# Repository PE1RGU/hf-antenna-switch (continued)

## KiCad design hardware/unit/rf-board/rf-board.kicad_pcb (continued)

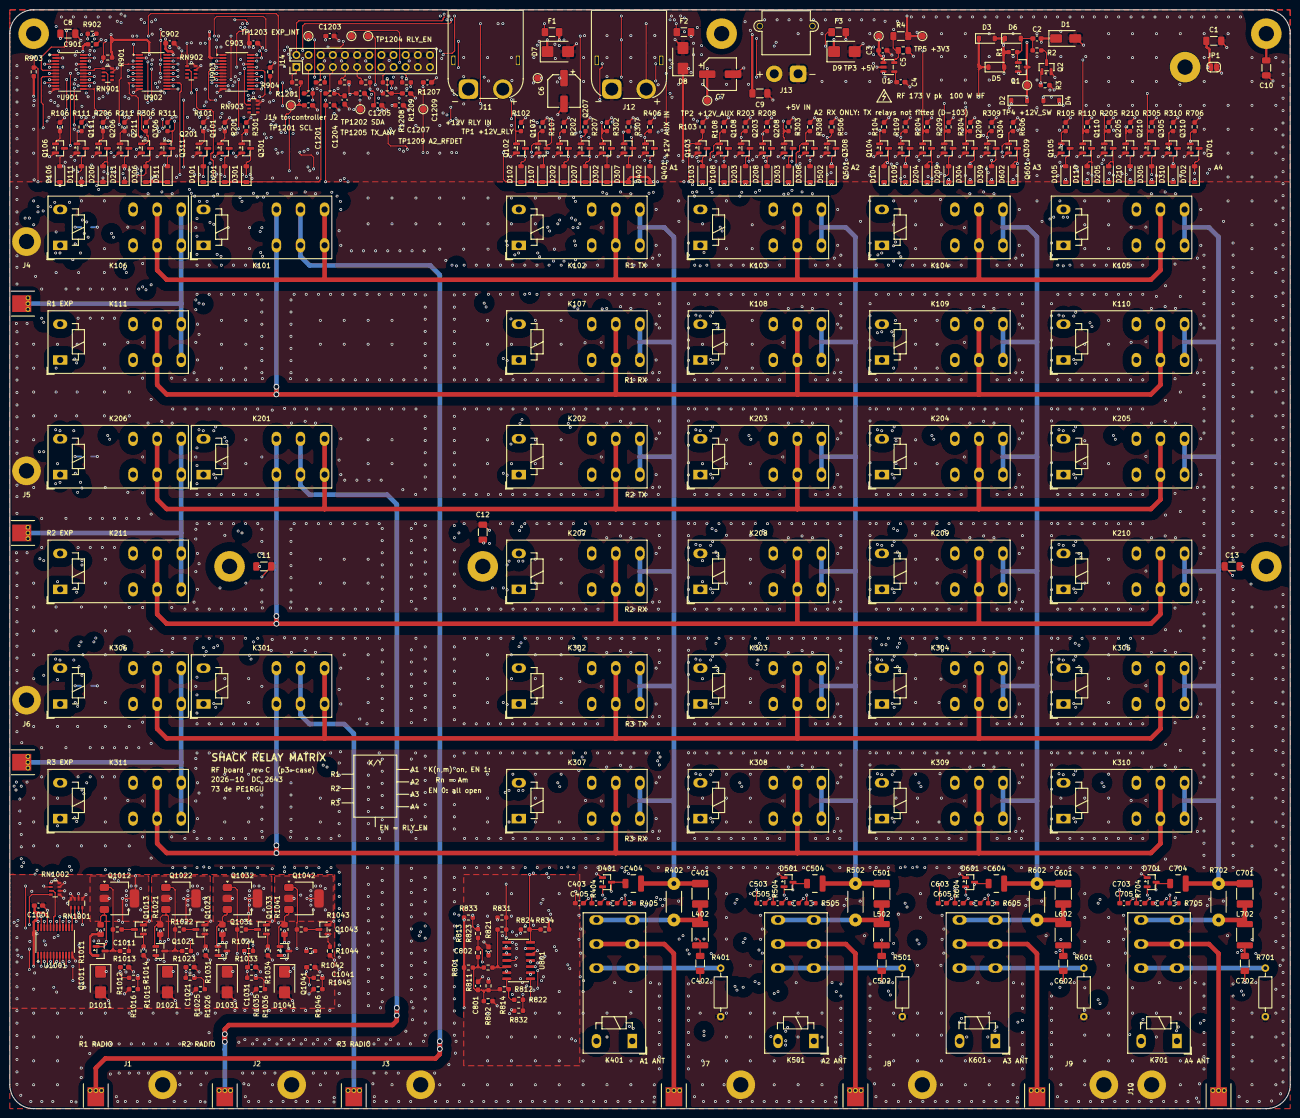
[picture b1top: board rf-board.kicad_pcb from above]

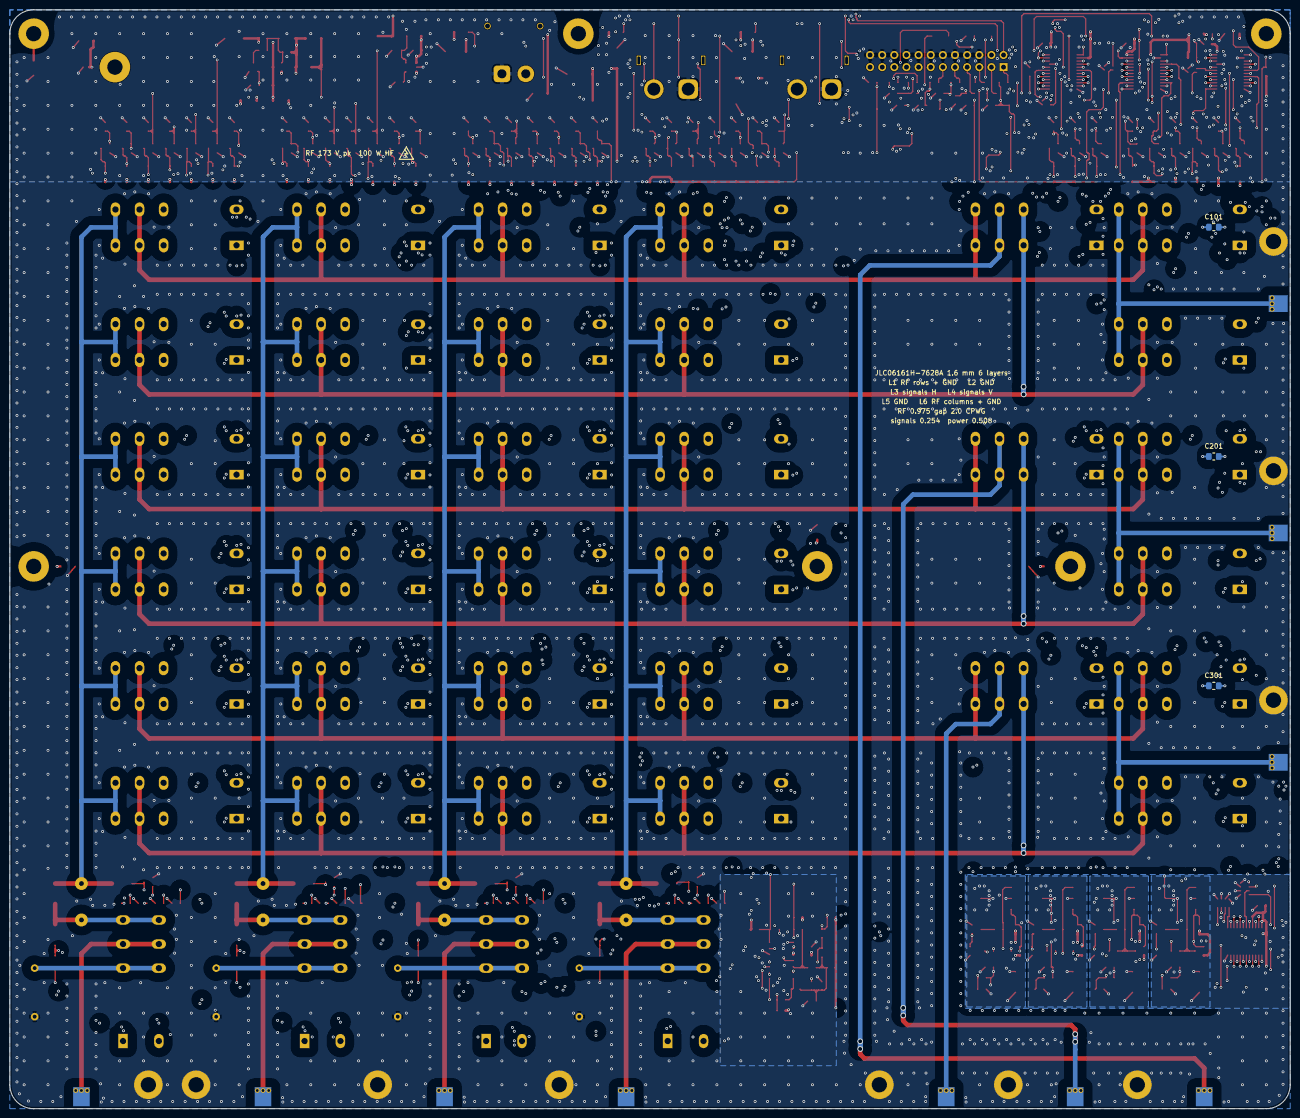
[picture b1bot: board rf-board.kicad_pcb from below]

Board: 6 copper layers, 268.0 x 230.0 mm, 357 parts (3 on the bottom side), 197 nets.

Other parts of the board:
CTL3D: controller board 3D (reference only)

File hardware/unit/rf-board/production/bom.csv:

Designator,Footprint,Quantity,Value,LCSC Part #
"C1001, C3, C802, C901, C902, C903",0603,6,1u 16V X7R,
"C101, C201, C301",0805,3,1u 50V X7R,
"C1011, C1021, C1031, C1041, C801",0603,5,100n 50V X7R,
"C4, C403, C503, C603, C703",0603,5,10n 50V X7R,
"C404, C504, C604, C704",1206,4,4.7p 1kV C0G,
"C405, C505, C605, C705",0603,4,47p 50V C0G,
C5,0805,1,4.7u 16V X7R,
"C6, C7",CP_Elec_6.3x7.7,2,47u 25V polymer,
D1,D_SMA,1,SS14,
"D101, D102, D104, D105, D106, D107, D108, D109, D110, D111, D201, D202, D204, D205, D206, D207, D208, D209, D210, D211, D301, D302, D304, D305, D306, D307, D308, D309, D310, D311, D402, D502, D602, D702",D_SOD-123,34,1N4148W,
"D1011, D1021, D1031, D1041, D7, D8",D_SMB,6,SMBJ15A,
"D2, D3, D4, D5",D_SOD-123,4,BZT52C24,
"D401, D501, D601, D701",SOT-23,4,BAS70-04,
D6,D_SOD-123,1,BZT52C15,
D9,D_SMB,1,SMBJ6.0A,
"F1, F2, F3",1206,3,1A T,
"J1, J2, J3, J7, J8, J9",SO239_83-798_StrapPad_BossRight,6,83-798 SO-239,
J10,SO239_83-798_StrapPad_BossLeft,1,83-798 SO-239,
"J11, J12",AMASS_XT60PW-M_1x02_P7.20mm_Horizontal,2,XT60PW-M,
J13,AMASS_XT30PW-M_1x02_P2.50mm_Horizontal,1,XT30PW-M,
J14,PinHeader_2x12_P2.54mm_Vertical,1,Controller header,
"J4, J5, J6",SMA_901-9215_StrapPad,3,SMA jack EXP,
"K101, K102, K104, K105, K106, K107, K108, K109, K110, K111, K201, K202, K204, K205, K206, K207, K208, K209, K210, K211, K301, K302, K304, K305, K306, K307, K308, K309, K310, K311, K401, K501, K601, K701",Relay_SPDT_Schrack-RT1-16A-FormC_RM5mm,34,RTD14012F,
Q1,SOT-23,1,PMV50EPEA,
"Q101, Q1013, Q102, Q1023, Q1033, Q104, Q1043, Q105, Q106, Q107, Q108, Q109, Q110, Q111, Q2, Q201, Q202, Q204, Q205, Q206, Q207, Q208, Q209, Q210, Q211, Q301, Q302, Q304, Q305, Q306, Q307, Q308, Q309, Q310, Q311, Q401, Q501, Q601, Q701",SOT-23,39,BSS138BK,
"Q1011, Q1021, Q1031, Q1041",SOT-23,4,BC857B,
"Q1012, Q1022, Q1032, Q1042",SOT-223-3_TabPin2,4,IRFL9014,
"R1, R1016, R1026, R1036, R1046, R801, R811, R812, R813, R814, R831, R832, R833, R834, R903",0603,15,10k,
"R101, R1012, R1014, R102, R1022, R1024, R1032, R1034, R104, R1042, R1044, R105, R106, R107, R108, R109, R110, R111, R201, R202, R204, R205, R206, R207, R208, R209, R210, R211, R3, R301, R302, R304, R305, R306, R307, R308, R309, R310, R311, R406, R506, R606, R706, R904",0603,44,100k,
"R1011, R1021, R1031, R1041",0805,4,10R,
"R1013, R1023, R1033, R1043, R404, R405, R504, R505, R604, R605, R704, R705",0603,12,47k,
"R1015, R1025, R1035, R1045",0603,4,33k,
"R1201, R1202, R1203, R1204, R1205, R1206, R1207, R1208, R1209",0603,9,0R,
"R2, R901, R902",0603,3,2k2,
R4,1206,1,0R,
"R401, R501, R601, R701",R_Axial_DIN0207_L6.3mm_D2.5mm_P10.16mm_Horizontal,4,1M HV,
"R402, R502, R602, R702",WireLink_P7.62mm_D1.0mm,4,0R wire link,
R802,0603,1,1k,
"R821, R822, R823, R824",0603,4,1M,
"RN1001, RN1002, RN901, RN902, RN903",R_Array_Convex_4x0603,5,10k x4,
U1,SOT-23-5,1,LP2985-33,
"U1001, U901, U902, U903",TSSOP-24_4.4x7.8mm_P0.65mm,4,PCA9539,
U801,SOIC-14_3.9x8.7mm_P1.27mm,1,LM2901,

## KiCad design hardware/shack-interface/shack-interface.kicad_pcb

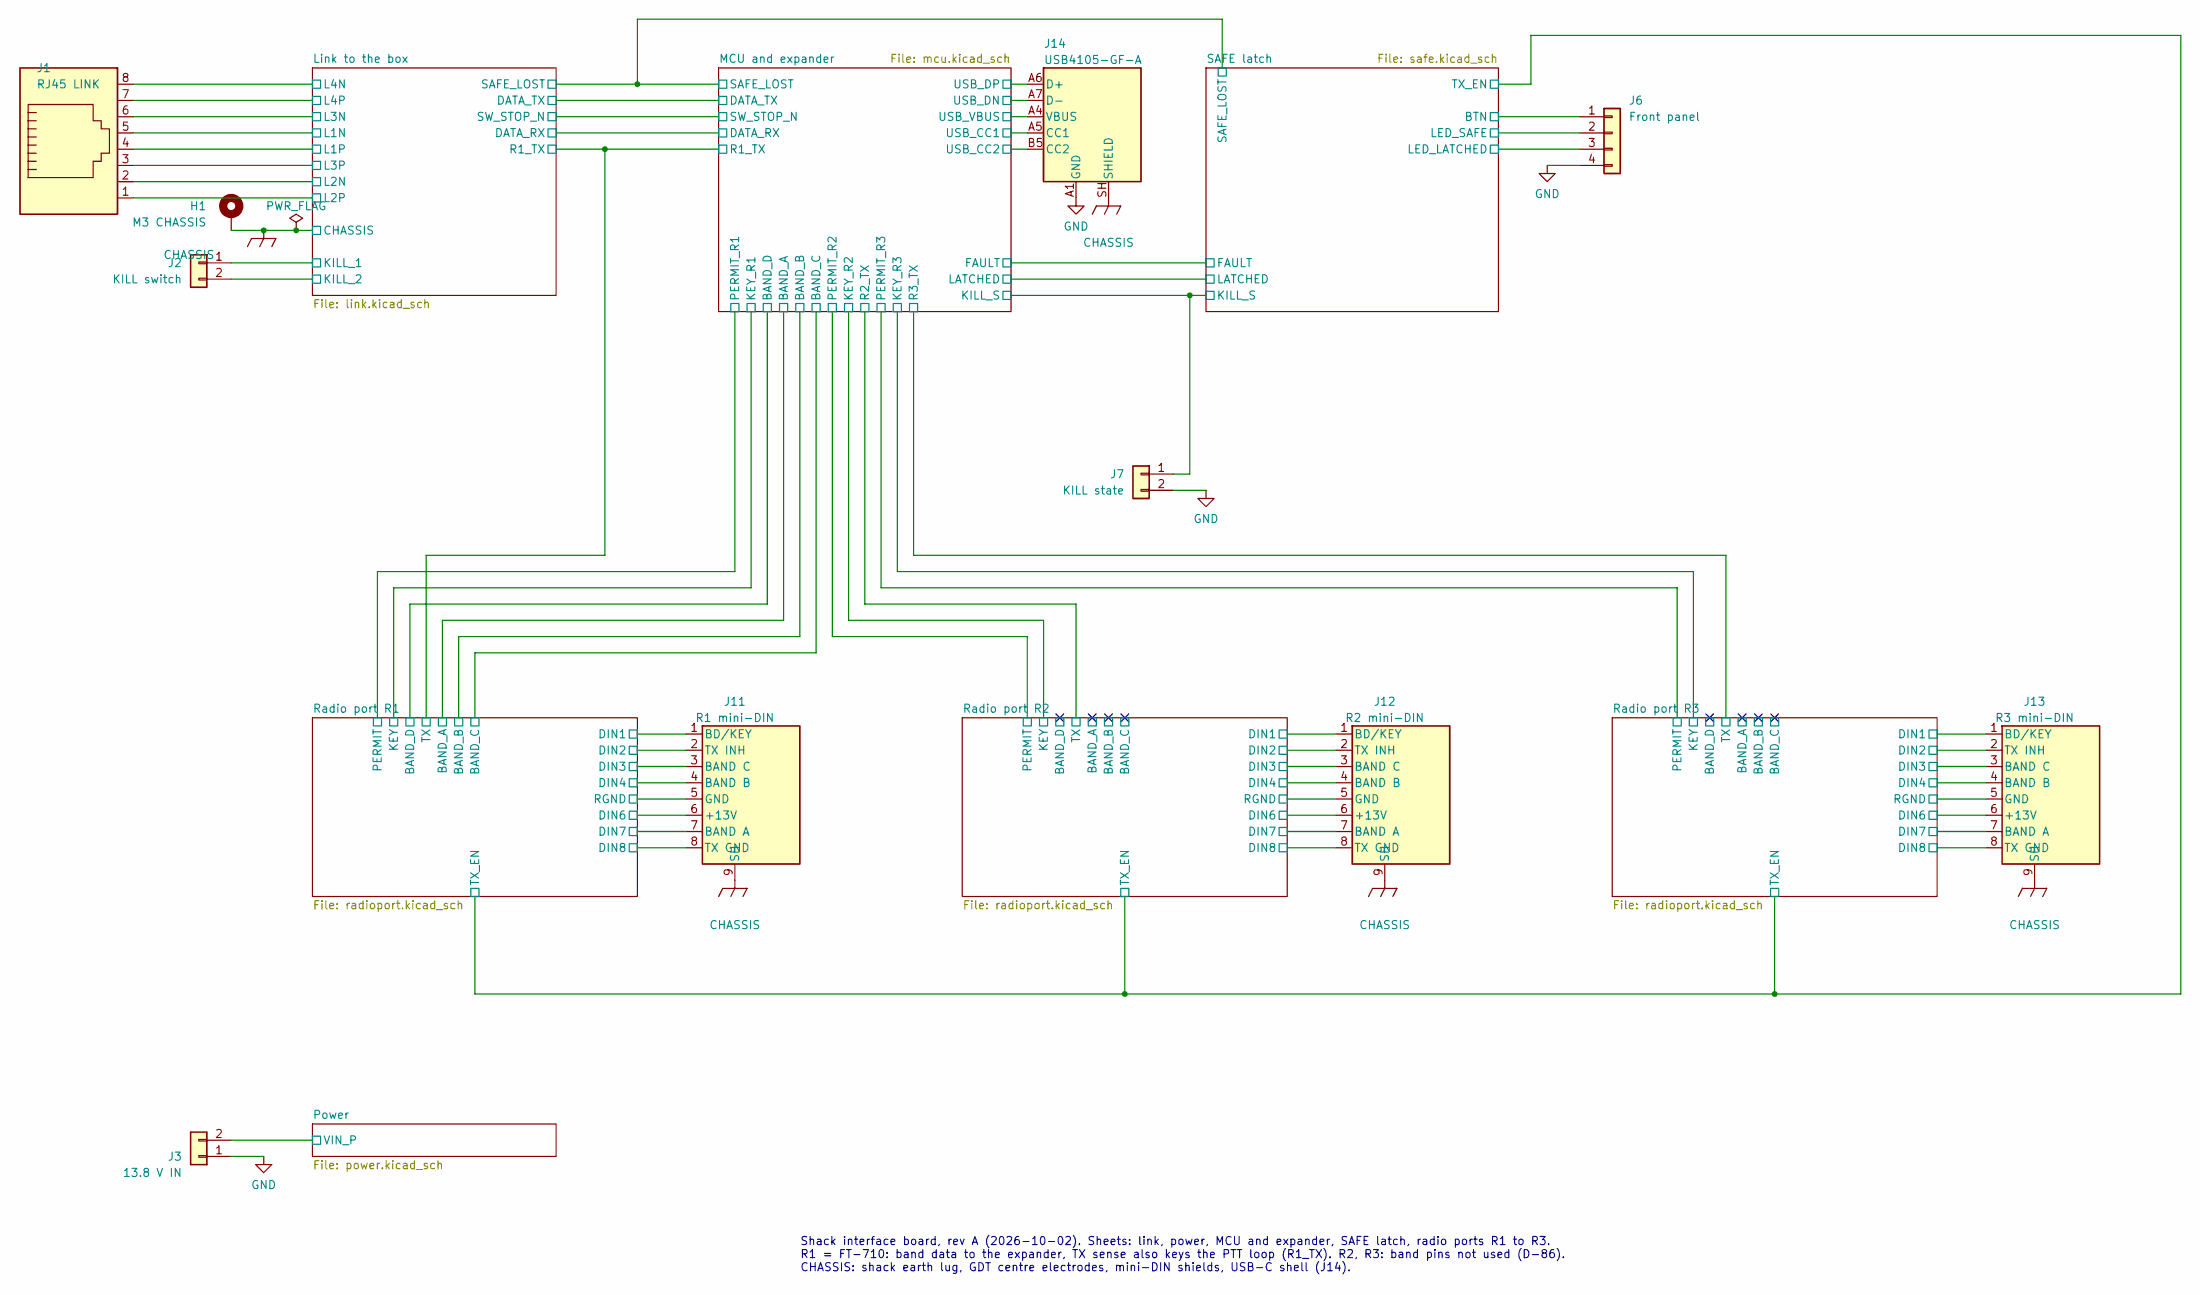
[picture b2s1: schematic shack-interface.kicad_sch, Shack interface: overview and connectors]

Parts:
H1: M3 CHASSIS; MountingHole_3.2mm_M3_Pad
J1: RJ45 LINK; RJ45_8P8C_Unshielded_TabDown; MPN 615008137121
J2: KILL switch; JST_XH_B2B-XH-A_1x02_P2.50mm_Vertical
J3: 13.8 V IN; AMASS_XT60PW-M_1x02_P7.20mm_Horizontal; MPN XT60PW-M
J6: Front panel; JST_XH_B4B-XH-A_1x04_P2.50mm_Vertical
J7: KILL state; JST_XH_B2B-XH-A_1x02_P2.50mm_Vertical
J11: R1 mini-DIN; MiniDIN-8_SameSky_MD-80SM_Horizontal; MPN MD-80SM
J12: R2 mini-DIN; MiniDIN-8_SameSky_MD-80SM_Horizontal; MPN MD-80SM
J13: R3 mini-DIN; MiniDIN-8_SameSky_MD-80SM_Horizontal; MPN MD-80SM
J14: USB4105-GF-A; USB_C_Receptacle_GCT_USB4105-xx-A_16P_TopMnt_Horizontal; MPN USB4105-GF-A

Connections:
/Link to the box/KILL_1: J2.1; also elsewhere on the board
/Link to the box/KILL_2: J2.2; also elsewhere on the board
/Link to the box/L1N: J1.5; also elsewhere on the board
/Link to the box/L1P: J1.4; also elsewhere on the board
/Link to the box/L2N: J1.2; also elsewhere on the board
/Link to the box/L2P: J1.1; also elsewhere on the board
/Link to the box/L3N: J1.6; also elsewhere on the board
/Link to the box/L3P: J1.3; also elsewhere on the board
/Link to the box/L4N: J1.8; also elsewhere on the board
/Link to the box/L4P: J1.7; also elsewhere on the board
/MCU and expander/KILL_S: J7.1; also elsewhere on the board
/MCU and expander/USB_CC1: J14.A5 (CC1); also elsewhere on the board
/MCU and expander/USB_CC2: J14.B5 (CC2); also elsewhere on the board
/MCU and expander/USB_DN: J14.A7 (D-), J14.B7 (D-); also elsewhere on the board
/MCU and expander/USB_DP: J14.A6 (D+), J14.B6 (D+); also elsewhere on the board
/MCU and expander/USB_VBUS: J14.A4 (VBUS), J14.A9 (VBUS), J14.B4 (VBUS), J14.B9 (VBUS); also elsewhere on the board
/Power/VIN_P: J3.2; also elsewhere on the board
/Radio port R1/DIN1: J11.1 (BD/KEY); also elsewhere on the board
/Radio port R1/DIN2: J11.2 (TX INH); also elsewhere on the board
/Radio port R1/DIN3: J11.3 (BAND C); also elsewhere on the board
/Radio port R1/DIN4: J11.4 (BAND B); also elsewhere on the board
/Radio port R1/DIN6: J11.6 (+13V); also elsewhere on the board
/Radio port R1/DIN7: J11.7 (BAND A); also elsewhere on the board
/Radio port R1/DIN8: J11.8 (TX GND); also elsewhere on the board
/Radio port R1/RGND: J11.5 (GND); also elsewhere on the board
/Radio port R2/DIN1: J12.1 (BD/KEY); also elsewhere on the board
/Radio port R2/DIN2: J12.2 (TX INH); also elsewhere on the board
/Radio port R2/DIN3: J12.3 (BAND C); also elsewhere on the board
/Radio port R2/DIN4: J12.4 (BAND B); also elsewhere on the board
/Radio port R2/DIN6: J12.6 (+13V); also elsewhere on the board
/Radio port R2/DIN7: J12.7 (BAND A); also elsewhere on the board
/Radio port R2/DIN8: J12.8 (TX GND); also elsewhere on the board
/Radio port R2/RGND: J12.5 (GND); also elsewhere on the board
/Radio port R3/DIN1: J13.1 (BD/KEY); also elsewhere on the board
/Radio port R3/DIN2: J13.2 (TX INH); also elsewhere on the board
/Radio port R3/DIN3: J13.3 (BAND C); also elsewhere on the board
/Radio port R3/DIN4: J13.4 (BAND B); also elsewhere on the board
/Radio port R3/DIN6: J13.6 (+13V); also elsewhere on the board
/Radio port R3/DIN7: J13.7 (BAND A); also elsewhere on the board
/Radio port R3/DIN8: J13.8 (TX GND); also elsewhere on the board
/Radio port R3/RGND: J13.5 (GND); also elsewhere on the board
/SAFE latch/BTN: J6.1; also elsewhere on the board
/SAFE latch/LED_LATCHED: J6.3; also elsewhere on the board
/SAFE latch/LED_SAFE: J6.2; also elsewhere on the board
CHASSIS: H1.1, J11.9 (SH), J12.9 (SH), J13.9 (SH), J14.SH (SHIELD); also elsewhere on the board
GND: J3.1, J6.4, J7.2, J14.A1 (GND), J14.A12 (GND), J14.B1 (GND), J14.B12 (GND); also elsewhere on the board

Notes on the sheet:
Shack interface board, rev A (2026-10-02). Sheets: link, power, MCU and expander, SAFE latch, radio ports R1 to R3. R1 = FT-710: band data to the expander, TX sense also keys the PTT loop (R1_TX). R2, R3: band pins not used (D-86). CHASSIS: shack earth lug, GDT centre electrodes, mini-DIN shields, 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

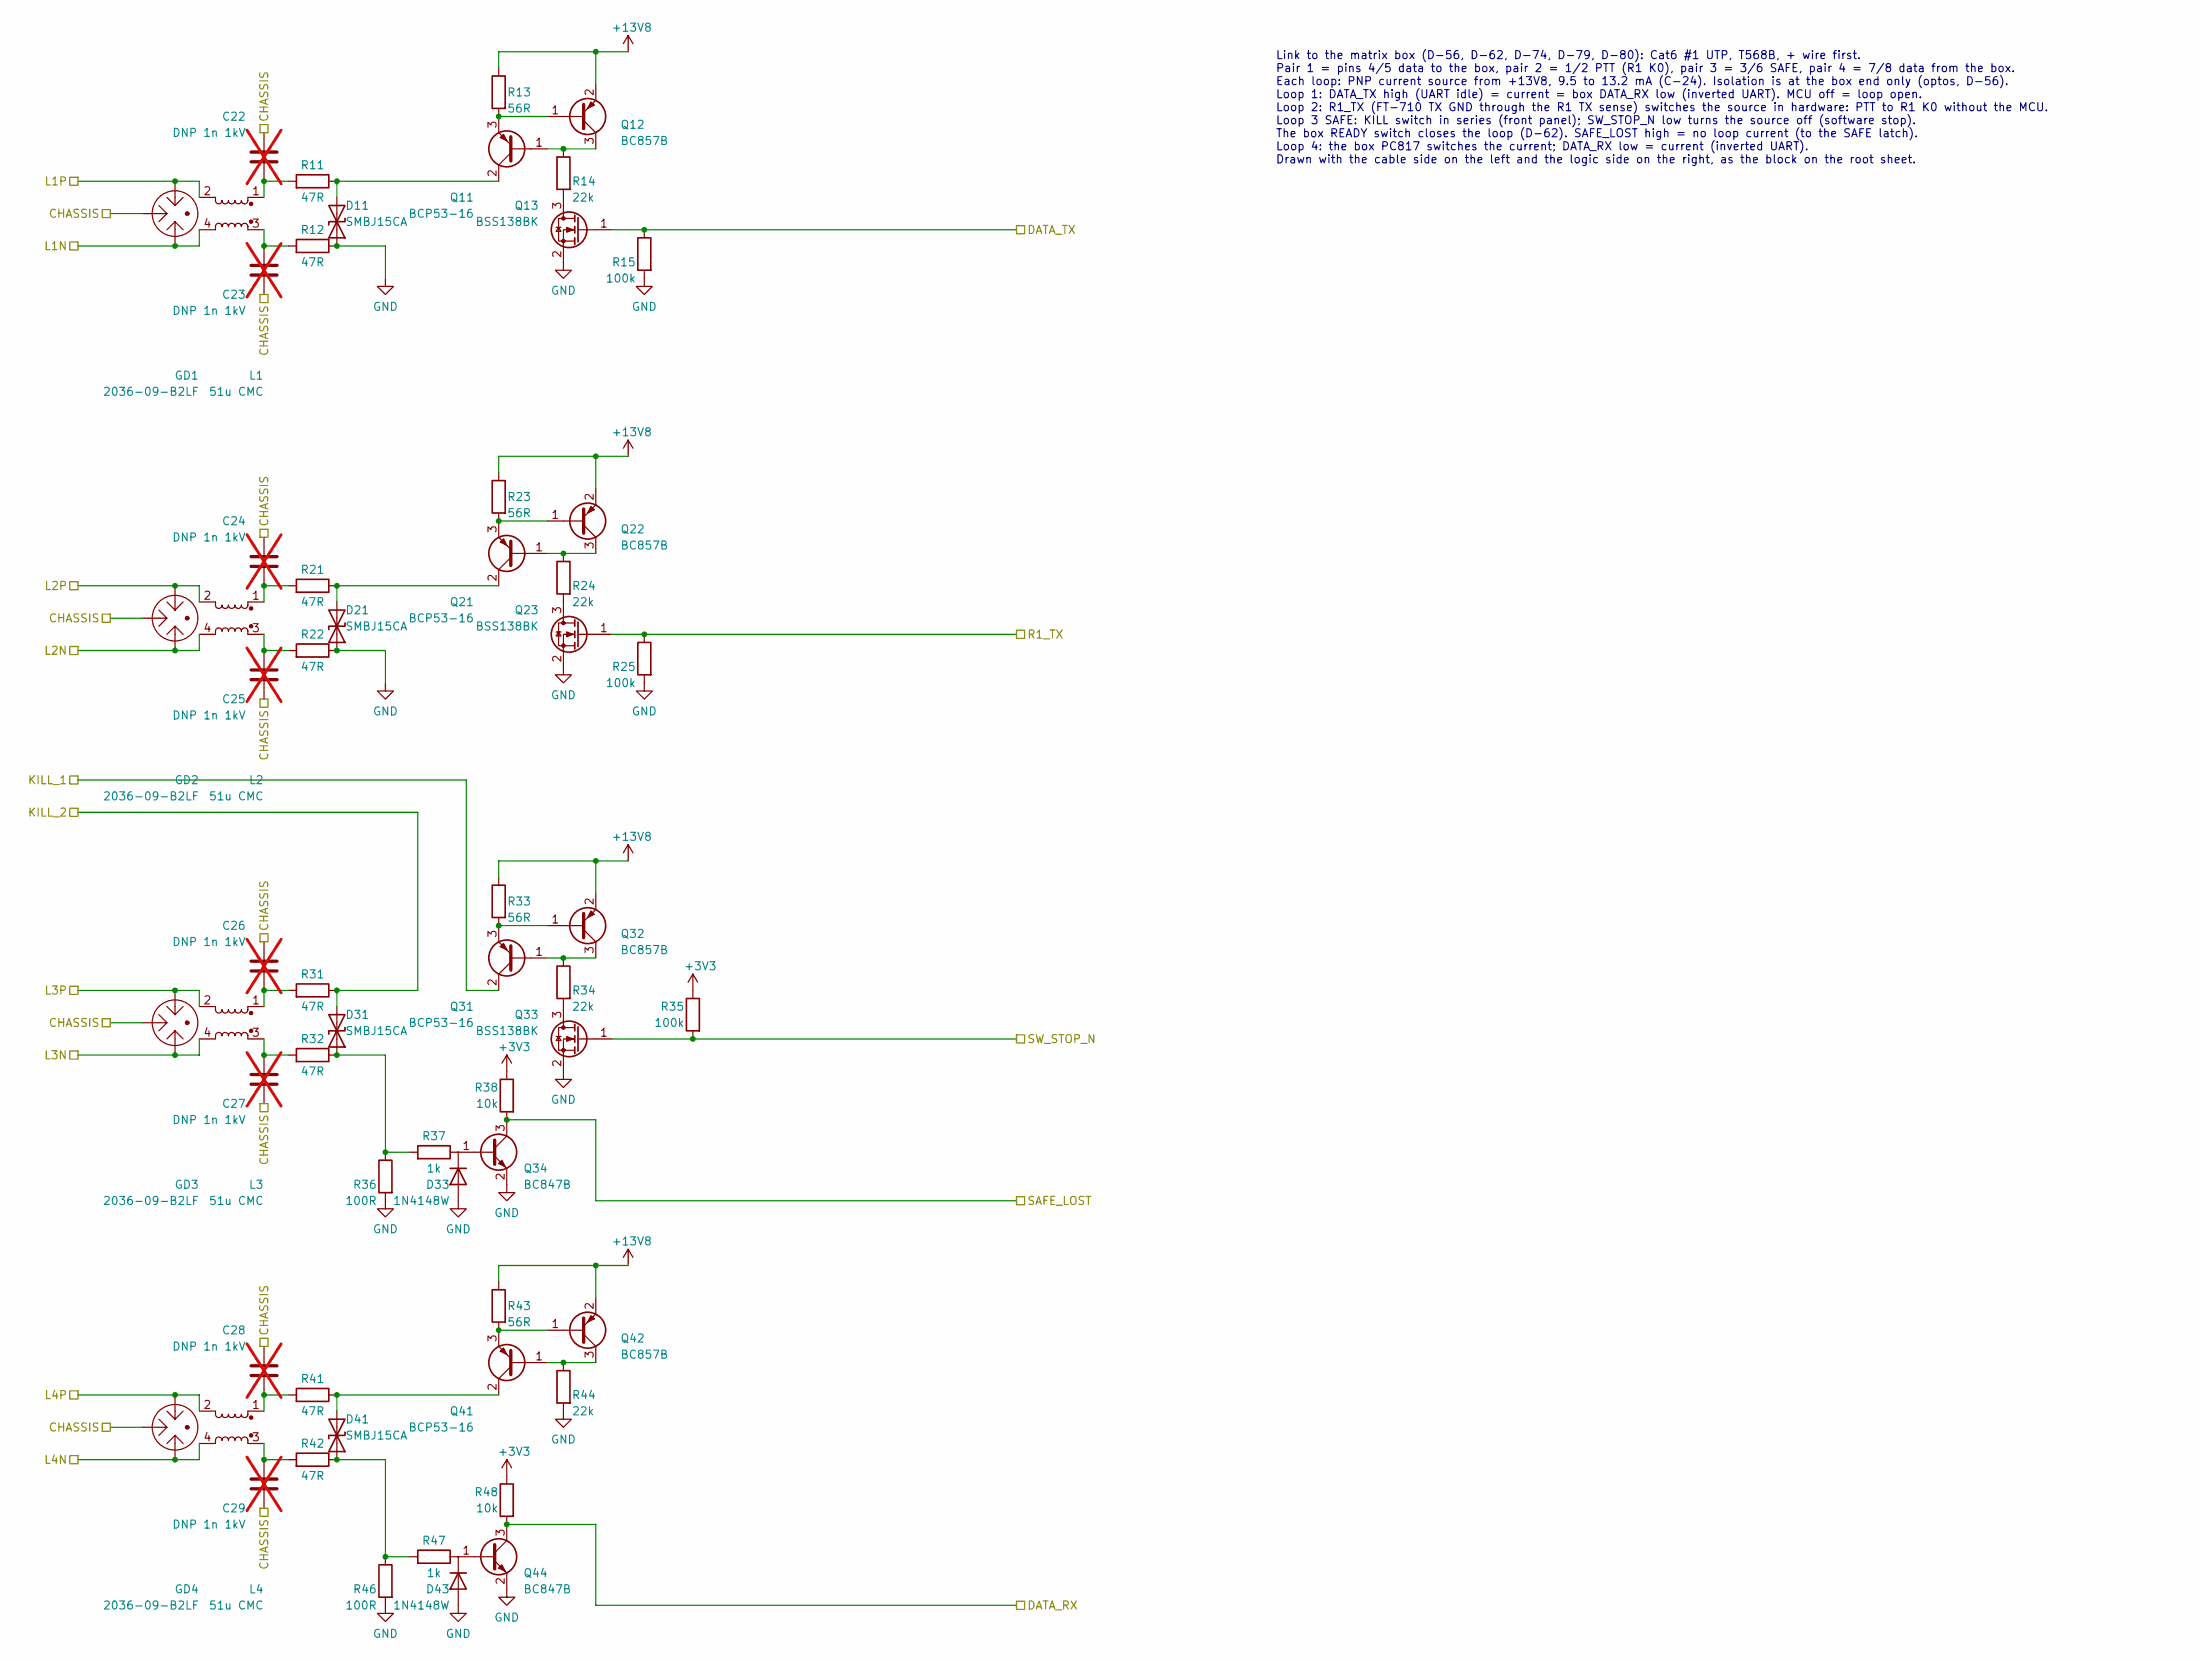
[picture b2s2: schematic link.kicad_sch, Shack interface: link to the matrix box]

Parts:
C22, C23, C24, C25, C26, C27, C28, C29: DNP 1n 1kV; C_1206_3216Metric_Pad1.33x1.80mm_HandSolder; not fitted
D11, D21, D31, D41: SMBJ15CA; D_SMB; MPN SMBJ15CA
D33, D43: 1N4148W; D_SOD-123; MPN 1N4148W
GD1, GD2, GD3, GD4: 2036-09-B2LF; GDT_3Pin_P4.40mm_Bourns-2036-B2_Littelfuse-SL1003A-R; MPN 2036-09-B2LF
L1, L2, L3, L4: 51u CMC; L_CMC_TDK_ACT45B; MPN ACT45B-510-2P-TL003
Q11, Q21, Q31, Q41: BCP53-16; SOT-223-3_TabPin2; MPN BCP53-16
Q12, Q22, Q32, Q42: BC857B; SOT-23; MPN BC857B
Q13, Q23, Q33: BSS138BK; SOT-23; MPN BSS138BK
Q34, Q44: BC847B; SOT-23; MPN BC847B
R11, R12, R21, R22, R31, R32, R41, R42: 47R; R_MELF_MMB-0207
R13, R23, R33, R43: 56R; R_0603_1608Metric_Pad0.98x0.95mm_HandSolder
R14, R24, R34, R44: 22k; R_0603_1608Metric_Pad0.98x0.95mm_HandSolder
R15, R25, R35: 100k; R_0603_1608Metric_Pad0.98x0.95mm_HandSolder
R36, R46: 100R; R_0603_1608Metric_Pad0.98x0.95mm_HandSolder
R37, R47: 1k; R_0603_1608Metric_Pad0.98x0.95mm_HandSolder
R38, R48: 10k; R_0603_1608Metric_Pad0.98x0.95mm_HandSolder

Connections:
+3V3: R35.1, R38.1, R48.1; also elsewhere on the board
+13V8: Q12.2 (E), Q22.2 (E), Q32.2 (E), Q42.2 (E), R13.1, R23.1, R33.1, R43.1; also elsewhere on the board
/Link to the box/KILL_1: Q31.2 (C); also elsewhere on the board
/Link to the box/KILL_2: D31.2 (A2), R31.1; also elsewhere on the board
/Link to the box/L1N: GD1.1, L1.4; also elsewhere on the board
/Link to the box/L1P: GD1.3, L1.2; also elsewhere on the board
/Link to the box/L2N: GD2.1, L2.4; also elsewhere on the board
/Link to the box/L2P: GD2.3, L2.2; also elsewhere on the board
/Link to the box/L3N: GD3.1, L3.4; also elsewhere on the board
/Link to the box/L3P: GD3.3, L3.2; also elsewhere on the board
/Link to the box/L4N: GD4.1, L4.4; also elsewhere on the board
/Link to the box/L4P: GD4.3, L4.2; also elsewhere on the board
/Link to the box/R1_TX: Q23.1 (G), R25.1; also elsewhere on the board
/Link to the box/SW_STOP_N: Q33.1 (G), R35.2; also elsewhere on the board
/MCU and expander/DATA_RX: Q44.3 (C), R48.2; also elsewhere on the board
/MCU and expander/DATA_TX: Q13.1 (G), R15.1; also elsewhere on the board
/MCU and expander/SAFE_LOST: Q34.3 (C), R38.2; also elsewhere on the board
CHASSIS: C22.1, C23.2, C24.1, C25.2, C26.1, C27.2, C28.1, C29.2, GD1.2, GD2.2, GD3.2, GD4.2; also elsewhere on the board
GND: D11.1 (A1), D21.1 (A1), D33.2 (A), D43.2 (A), Q13.2 (S), Q23.2 (S), Q33.2 (S), Q34.2 (E), Q44.2 (E), R12.1, R15.2, R22.1, R25.2, R36.2, R44.2, R46.2; also elsewhere on the board
unnamed: C22.2, L1.1, R11.2
unnamed: C23.1, L1.3, R12.2
unnamed: C24.2, L2.1, R21.2
unnamed: C25.1, L2.3, R22.2
unnamed: C26.2, L3.1, R31.2
unnamed: C27.1, L3.3, R32.2
unnamed: C28.2, L4.1, R41.2
unnamed: C29.1, L4.3, R42.2
unnamed: D11.2 (A2), Q11.2 (C), R11.1
unnamed: D21.2 (A2), Q21.2 (C), R21.1
unnamed: D31.1 (A1), R32.1, R36.1, R37.2
unnamed: D33.1 (K), Q34.1 (B), R37.1
unnamed: D41.1 (A1), R42.1, R46.1, R47.2
unnamed: D41.2 (A2), Q41.2 (C), R41.1
unnamed: D43.1 (K), Q44.1 (B), R47.1
unnamed: Q11.1 (B), Q12.3 (C), R14.1
unnamed: Q11.3 (E), Q12.1 (B), R13.2
unnamed: Q13.3 (D), R14.2
unnamed: Q21.1 (B), Q22.3 (C), R24.1
unnamed: Q21.3 (E), Q22.1 (B), R23.2
unnamed: Q23.3 (D), R24.2
unnamed: Q31.1 (B), Q32.3 (C), R34.1
unnamed: Q31.3 (E), Q32.1 (B), R33.2
unnamed: Q33.3 (D), R34.2
unnamed: Q41.1 (B), Q42.3 (C), R44.1
unnamed: Q41.3 (E), Q42.1 (B), R43.2

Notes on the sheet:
Link to the matrix box (D-56, D-62, D-74, D-79, D-80): Cat6 #1 UTP, T568B, + wire first. Pair 1 = pins 4/5 data to the box, pair 2 = 1/2 PTT (R1 K0), pair 3 = 3/6 SAFE, pair 4 = 7/8 data from the box. Each loop: PNP current source from +13V8, 9.5 to 13.2 mA (C-24). Isolation is at the box end only 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

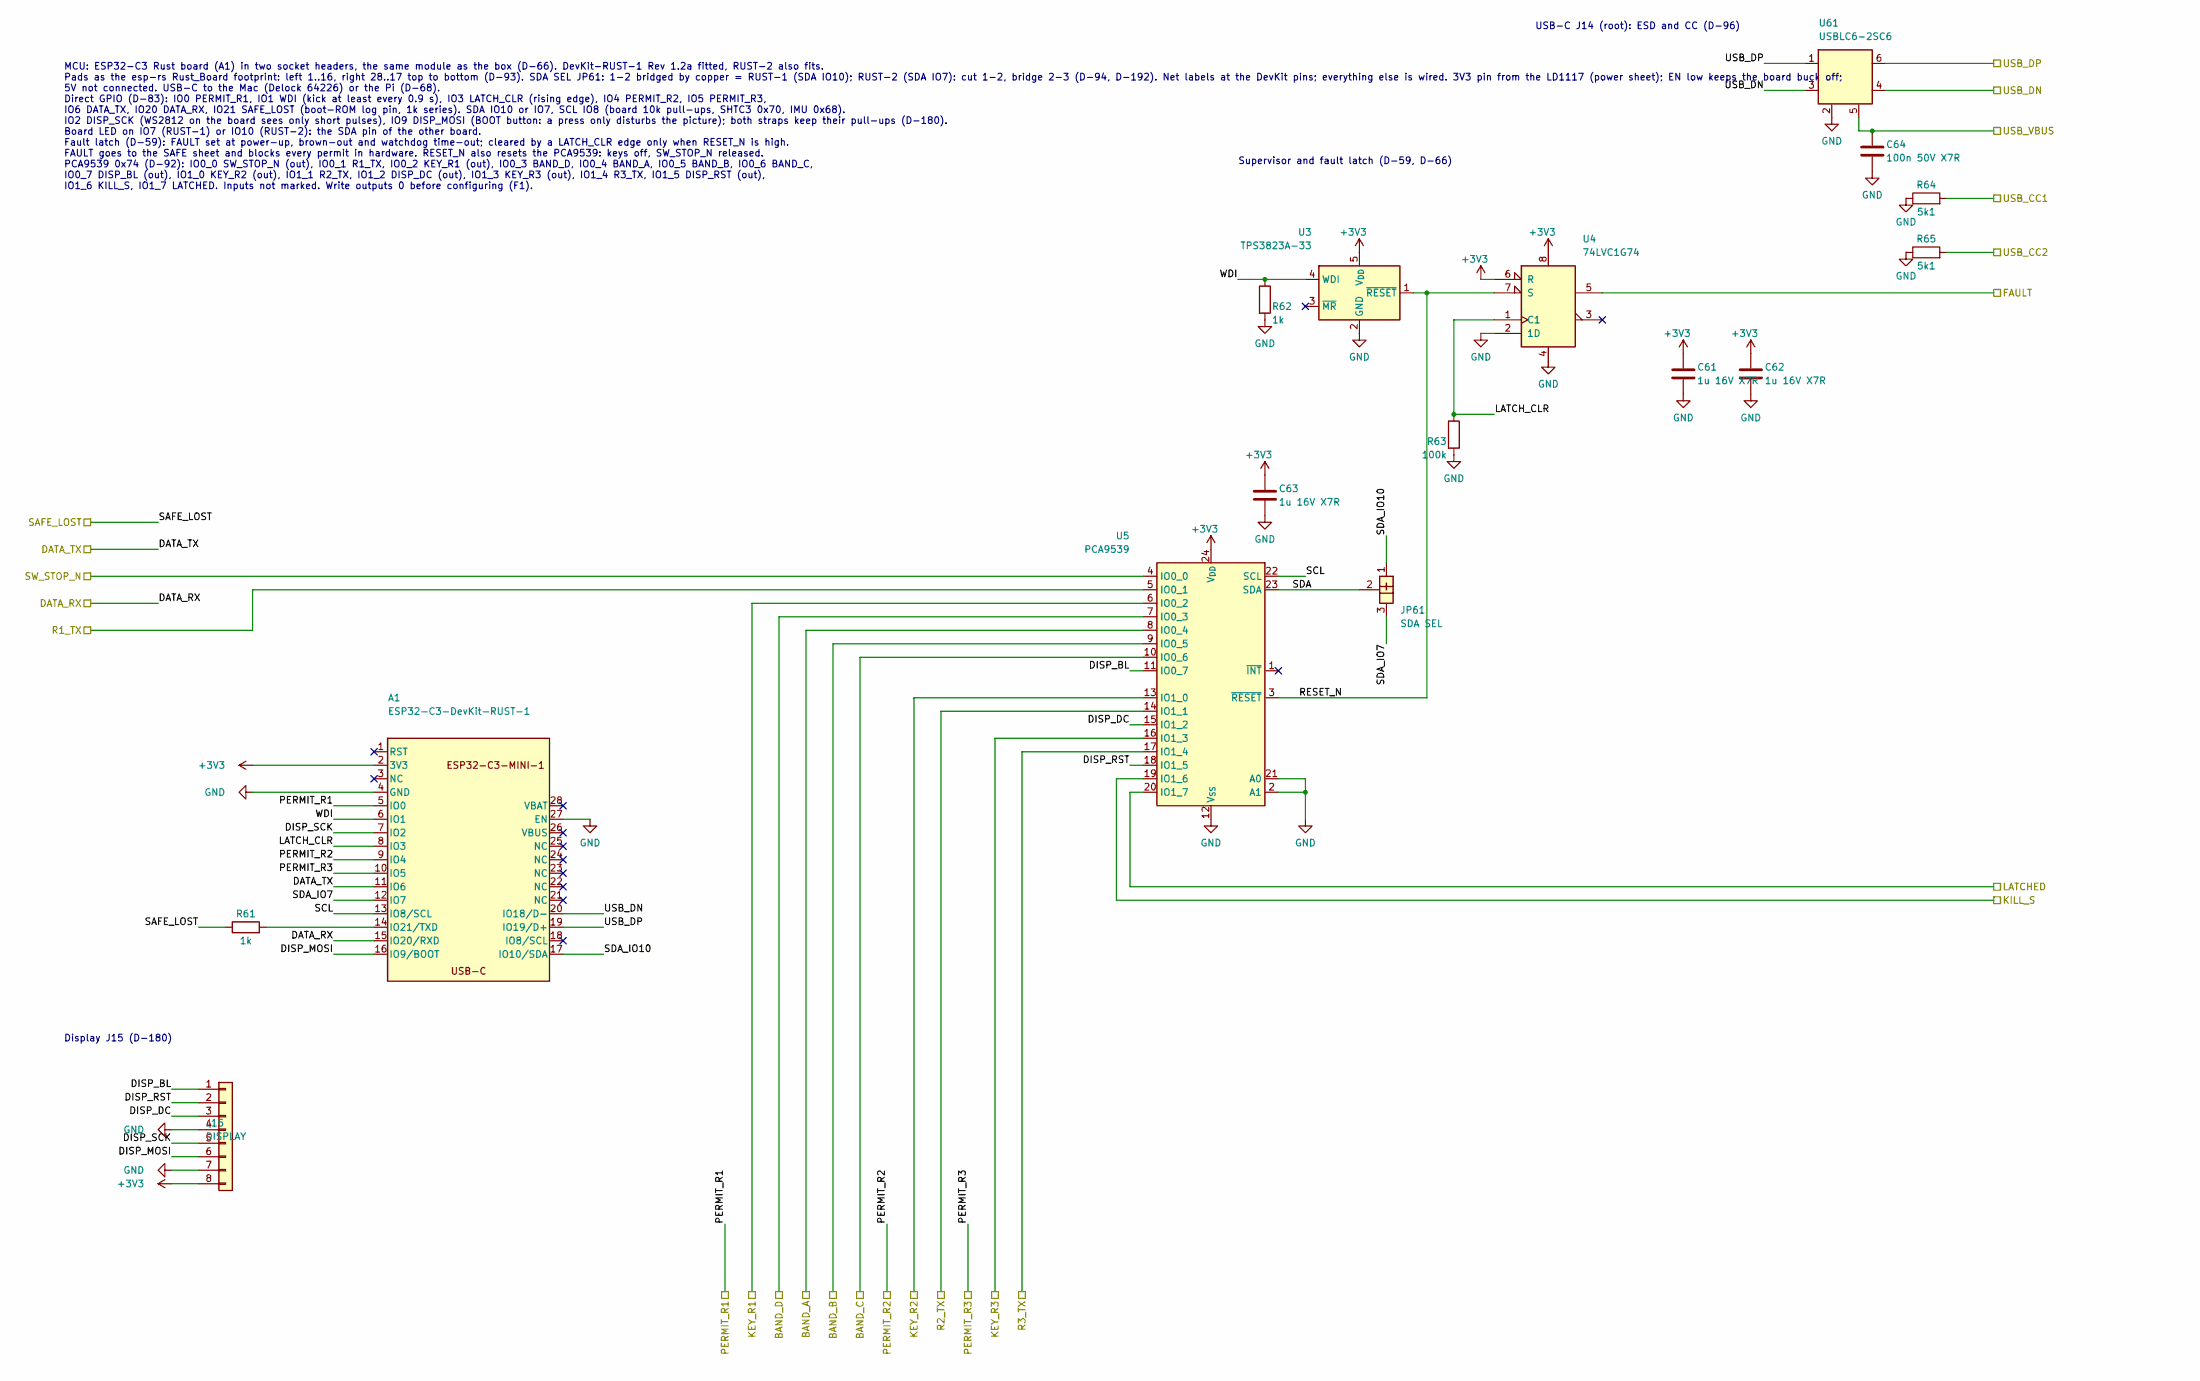
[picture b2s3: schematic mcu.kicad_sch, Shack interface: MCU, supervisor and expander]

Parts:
A1: ESP32-C3-DevKit-RUST-1; ESP32-C3-DevKit-RUST_Socket
C61, C62, C63: 1u 16V X7R; C_0603_1608Metric_Pad1.08x0.95mm_HandSolder
C64: 100n 50V X7R; C_0603_1608Metric_Pad1.08x0.95mm_HandSolder
J15: DISPLAY; PinHeader_1x08_P2.54mm_Vertical
JP61: SDA SEL; SolderJumper-3_P1.3mm_Bridged12_RoundedPad1.0x1.5mm_NumberL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
R61, R62: 1k; R_0603_1608Metric_Pad0.98x0.95mm_HandSolder
R63: 100k; R_0603_1608Metric_Pad0.98x0.95mm_HandSolder
R64, R65: 5k1; R_0603_1608Metric_Pad0.98x0.95mm_HandSolder
U3: TPS3823A-33; SOT-23-5; MPN TPS3823A-33DBVR
U4: 74LVC1G74; VSSOP-8_2.3x2mm_P0.5mm; MPN SN74LVC1G74DCUR
U5: PCA9539; TSSOP-24_4.4x7.8mm_P0.65mm; MPN PCA9539PW,118
U61: USBLC6-2SC6; SOT-23-6; MPN USBLC6-2SC6

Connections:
+3V3: A1.2 (3V3), C61.1, C62.1, C63.1, J15.8, U3.5 (V_{DD}), U4.6 (R), U4.8, U5.24 (V_{DD}); also elsewhere on the board
/Link to the box/R1_TX: U5.5 (IO0_1); also elsewhere on the board
/Link to the box/SW_STOP_N: U5.4 (IO0_0); also elsewhere on the board
/MCU and expander/BAND_A: U5.8 (IO0_4); also elsewhere on the board
/MCU and expander/BAND_B: U5.9 (IO0_5); also elsewhere on the board
/MCU and expander/BAND_C: U5.10 (IO0_6); also elsewhere on the board
/MCU and expander/BAND_D: U5.7 (IO0_3); also elsewhere on the board
/MCU and expander/DATA_RX: A1.15 (IO20/RXD); also elsewhere on the board
/MCU and expander/DATA_TX: A1.11 (IO6); also elsewhere on the board
/MCU and expander/DISP_BL: J15.1, U5.11 (IO0_7)
/MCU and expander/DISP_DC: J15.3, U5.15 (IO1_2)
/MCU and expander/DISP_MOSI: A1.16 (IO9/BOOT), J15.6
/MCU and expander/DISP_RST: J15.2, U5.18 (IO1_5)
/MCU and expander/DISP_SCK: A1.7 (IO2), J15.5
/MCU and expander/FAULT: U4.5; also elsewhere on the board
/MCU and expander/KEY_R1: U5.6 (IO0_2); also elsewhere on the board
/MCU and expander/KEY_R2: U5.13 (IO1_0); also elsewhere on the board
/MCU and expander/KEY_R3: U5.16 (IO1_3); also elsewhere on the board
/MCU and expander/KILL_S: U5.19 (IO1_6); also elsewhere on the board
/MCU and expander/LATCHED: U5.20 (IO1_7); also elsewhere on the board
/MCU and expander/LATCH_CLR: A1.8 (IO3), R63.1, U4.1 (C1)
/MCU and expander/PERMIT_R1: A1.5 (IO0); also elsewhere on the board
/MCU and expander/PERMIT_R2: A1.9 (IO4); also elsewhere on the board
/MCU and expander/PERMIT_R3: A1.10 (IO5); also elsewhere on the board
/MCU and expander/R2_TX: U5.14 (IO1_1); also elsewhere on the board
/MCU and expander/R3_TX: U5.17 (IO1_4); also elsewhere on the board
/MCU and expander/RESET_N: U3.1 (~RESET), U4.7 (S), U5.3 (~RESET)
/MCU and expander/SAFE_LOST: R61.1; also elsewhere on the board
/MCU and expander/SCL: A1.13 (IO8/SCL), U5.22 (SCL)
/MCU and expander/SDA: JP61.2, U5.23 (SDA)
/MCU and expander/SDA_IO7: A1.12 (IO7), JP61.3
/MCU and expander/SDA_IO10: A1.17 (IO10/SDA), JP61.1
/MCU and expander/USB_CC1: R64.2; also elsewhere on the board
/MCU and expander/USB_CC2: R65.2; also elsewhere on the board
/MCU and expander/USB_DN: A1.20 (IO18/D-), U61.3 (I/O2), U61.4 (I/O2); also elsewhere on the board
/MCU and expander/USB_DP: A1.19 (IO19/D+), U61.1 (I/O1), U61.6 (I/O1); also elsewhere on the board
/MCU and expander/USB_VBUS: C64.1, U61.5 (VBUS); also elsewhere on the board
/MCU and expander/WDI: A1.6 (IO1), R62.1, U3.4 (WDI)
GND: A1.4 (GND), A1.27 (EN), C61.2, C62.2, C63.2, C64.2, J15.4, J15.7, R62.2, R63.2, R64.1, R65.1, U3.2 (GND), U4.2 (1D), U4.4, U5.2 (A1), U5.12 (V_{SS}), U5.21 (A0), U61.2 (GND); also elsewhere on the board
unnamed: A1.14 (IO21/TXD), R61.2

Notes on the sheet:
Supervisor and fault latch (D-59, D-66)
USB-C J14 (root): ESD and CC (D-96)
Display J15 (D-180)
MCU: ESP32-C3 Rust board (A1) in two socket headers, the same module as the box (D-66). DevKit-RUST-1 Rev 1.2a fitted, RUST-2 also fits. Pads as the esp-rs Rust_Board footprint: left 1..16, right 28..17 top to bottom (D-93). SDA SEL JP61: 1-2 bridged by copper = RUST-1 (SDA IO10); RUST-2 (SDA IO7):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
